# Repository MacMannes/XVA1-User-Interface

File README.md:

# XVA1 User Interface

A hardware user interface for the [XVA1 virtual analog synthesizer](https://www.futur3soundz.com/), inspired by the Hydrasynth's layout. The XVA1 (and its FM sibling the XFM2) is built on an Artix-7 FPGA but has no built-in UI — this project adds one.

## Overview

The UI board provides:

- **1 main rotary encoder** — patch selection and menu navigation
- **8 parameter rotary encoders** — control up to 8 synth parameters at once
- **4 OLED displays (128×64)** — show parameter names and values for each encoder pair
- **1 TFT display (240×240)** — main display showing patch name, section, and subsection
- **8 shortcut buttons with LEDs** — jump directly to parameter sections (Oscillators, Filters, Envelopes, LFOs, etc.). Hold SHIFT + buttons 1–4 to access sections 9–12
- **Up/Down buttons with LEDs** — scroll through parameter pages within a section

The design goal was minimal menu-diving: select a section with one button press, then tweak up to eight parameters directly with the encoders.

## Hardware

- **MCU:** Seeed XIAO ESP32-S3 (240 MHz, dual-core)
- **IO expansion:** 2× MCP23017 (the 8 parameter encoders connect via I2C)
- **Display mux:** TCA9548A I2C multiplexer for the 4 OLED displays
- **Synth connection:** UART at 500,000 baud (D6 TX, D7 RX)
- **PCB size:** 285 mm × 130 mm
- **Buttons:** PB86-B1 (with LED) / PB86-B0 (without LED), available from AliExpress

KiCad schematics are in the `Hardware/` directory.

## Build History

The project started in early 2021 on a breadboard with a Seeeduino XIAO (SAMD21), then moved to an ESP32 devboard when memory became a bottleneck, and eventually settled on the **Seeed XIAO ESP32-S3** as a drop-in replacement with the same footprint. The first PCB prototype was ordered from JLCPCB and had a few minor errors (MIDI DIN pin swap, resistor silkscreen mix-up) that were corrected in subsequent revisions.

## Software

### UI Board Firmware

Firmware source is in `Software/XVA1UserInterface/` and built with [PlatformIO](https://platformio.org/).

```bash
# Run from Software/XVA1UserInterface/
platformio run                  # compile
platformio run -t upload        # compile and flash
platformio run -t monitor       # open serial monitor (115200 baud)
./upload_and_monitor.sh         # flash then monitor
```

See `AGENTS.md` for a full architecture breakdown and development notes.

### Use in Neovim

In order to use this project in Neovim, you will have to create the file `compile_commands.json`
file by running the following command:

```bash
pio run -t compiledb
```

### Synth Management

To manage the XVA1 (or XFM/XFM2) synthesizer's own firmware and programs, use [**xload-macos**](https://github.com/MacMannes/xload-macos) — a macOS tool for managing flash memory on XFM/XFM2/XVA1 synthesizers.

## Project Structure

```
Hardware/       KiCad schematics and datasheets
Docs/           Photos of front and back of the board
Software/
  XVA1UserInterface/   PlatformIO project (all firmware lives here)
```

## Status

Working prototype. Most parameters are implemented and editable. Patch saving is not yet implemented. The PCB design has gone through two revisions; the current version uses the XIAO ESP32-S3.

## License

See `LICENSE.md`.

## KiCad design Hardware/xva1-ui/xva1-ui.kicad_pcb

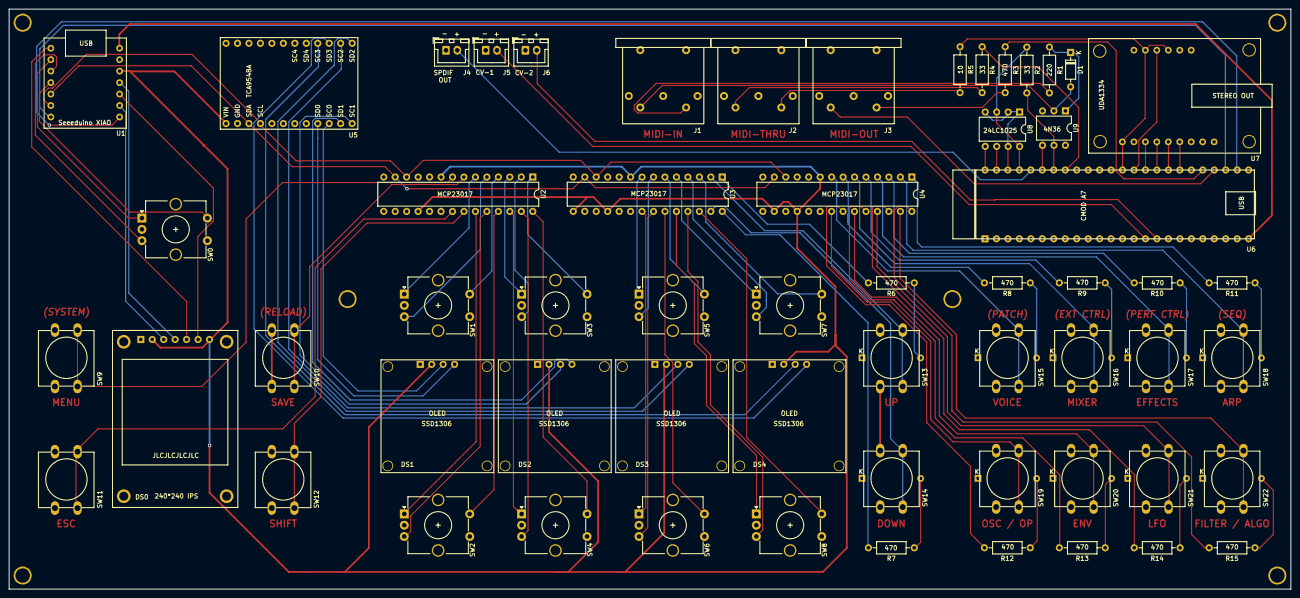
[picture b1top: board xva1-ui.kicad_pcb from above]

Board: 2 copper layers, 284.0 x 128.5 mm, 59 parts (0 on the bottom side), 104 nets.

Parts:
D1: 1N4148; D_DO-35_SOD27_P7.62mm_Horizontal
DS0: TFT_ST7789; TFT_IPS-240_240
DS1, DS2, DS3, DS4: SSD1306
J1, J2, J3: DIN-5_180degree; MIDI_CONNECTOR_PCB
J4, J5, J6: Conn_01x02; JST_XH_B2B-XH-A_1x02_P2.50mm_Vertical
R1: 220; R_Axial_DIN0207_L6.3mm_D2.5mm_P10.16mm_Horizontal
R2, R6, R7, R8, R9, R10, R11, R12, R13, R14, R15: 470; R_Axial_DIN0207_L6.3mm_D2.5mm_P10.16mm_Horizontal
R3, R4: 33; R_Axial_DIN0207_L6.3mm_D2.5mm_P10.16mm_Horizontal
R5: 10; R_Axial_DIN0207_L6.3mm_D2.5mm_P10.16mm_Horizontal
SW0, SW1, SW2, SW3, SW4, SW5, SW6, SW7, SW8: Rotary Encoder; RotaryEncoder_Alps_EC12E-Switch_Vertical_H20mm_CircularMoun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
SW9, SW10, SW11, SW12: SW_Push; SW_PUSH-12mm
SW13, SW14, SW15, SW16, SW17, SW18, SW19, SW20, SW21, SW22: SW_Push_LED; SW_PUSH_LED-12mm
U1: Seeeduino XIAO; Seeduino_XIAO_Through-Hole
U2, U3, U4: MCP23017; DIP-28_W7.62mm
U5: TCA9548A; TCA9548A_BREAKOUT
U6: CMOD-A7; CMOD-A7-DIP-48_W15.24mm
U7: UDA1334
U8: 24LC1025-I/P; DIP-8_W7.62mm
U9: 4N36; DIP-6_W7.62mm

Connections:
+3V3: DS0.2, DS0.7, DS1.2, DS2.2, DS3.2, DS4.2, U1.12, U2.9, U2.18, U3.9, U3.15, U3.18, U4.9, U4.16, U4.18, U5.1
+5V: U1.14, U6.24
/BTN-ESC: SW11.2, U2.21
/BTN-MENU: SW9.2, U2.8
/BTN-SAVE: SW10.2, U2.7
/BTN-SHIFT: SW12.2, U2.22
/ENC-A: SW0.A, U1.2
/ENC-B: SW0.B, U1.3
/ENC-S: SW0.S1, U1.4
/SCL: U1.6, U2.12, U3.12, U4.12, U5.4
/SDA: U1.5, U2.13, U3.13, U4.13, U5.3
BTN-DWN: SW14.2, U3.27
BTN-SC1: SW15.2, U4.8
BTN-SC2: SW16.2, U4.6
BTN-SC3: SW17.2, U4.4
BTN-SC4: SW18.2, U4.2
BTN-SC5: SW19.2, U4.21
BTN-SC6: SW20.2, U4.23
BTN-SC7: SW21.2, U4.25
BTN-SC8: SW22.2, U4.27
BTN-UP: SW13.2, U3.2
CV-INPUT-1: J5.2, U6.15
CV-INPUT-2: J6.2, U6.16
ENC1-A: SW1.A, U2.6
ENC1-B: SW1.B, U2.5
ENC1-S: SW1.S1, U2.4
ENC2-A: SW2.A, U2.23
ENC2-B: SW2.B, U2.24
ENC2-S: SW2.S1, U2.25
ENC3-A: SW3.A, U2.3
ENC3-B: SW3.B, U2.2
ENC3-S: SW3.S1, U2.1
ENC4-A: SW4.A, U2.26
ENC4-B: SW4.B, U2.27
ENC4-S: SW4.S1, U2.28
ENC5-A: SW5.A, U3.8
ENC5-B: SW5.B, U3.7
ENC5-S: SW5.S1, U3.6
ENC6-A: SW6.A, U3.21
ENC6-B: SW6.B, U3.22
ENC6-S: SW6.S1, U3.23
ENC7-A: SW7.A, U3.5
ENC7-B: SW7.B, U3.4
ENC7-S: SW7.S1, U3.3
ENC8-A: SW8.A, U3.24
ENC8-B: SW8.B, U3.25
ENC8-S: SW8.S1, U3.26
GND: DS0.1, DS1.1, DS2.1, DS3.1, DS4.1, J4.1, J5.1, J6.1, SW0.C, SW0.S2, SW1.C, SW1.S2, SW2.C, SW2.S2, SW3.C, SW3.S2, SW4.C, SW4.S2, SW5.C, SW5.S2, SW6.C, SW6.S2, SW7.C, SW7.S2, SW8.C, SW8.S2, SW9.1, SW10.1, SW11.1, SW12.1, SW13.1, SW13.3, SW14.1, SW14.3, SW15.1, SW15.3, SW16.1, SW16.3, SW17.1, SW17.3, SW18.1, SW18.3, SW19.1, SW19.3, SW20.1, SW20.3, SW21.1, SW21.3, SW22.1, SW22.3, U1.13, U2.10, U2.15, U2.16, U2.17, U3.10, U3.16, U3.17, U4.10, U4.15, U4.17, U5.2, U6.25
LED-DWN: R7.2, U3.28
LED-SC1: R8.2, U4.7
LED-SC2: R9.2, U4.5
LED-SC3: R10.2, U4.3
LED-SC4: R11.2, U4.1
LED-SC5: R12.2, U4.22
LED-SC6: R13.2, U4.24
LED-SC7: R14.2, U4.26
LED-SC8: R15.2, U4.28
LED-UP: R6.2, U3.1
unnamed: D1.1, R1.1, U9.1
unnamed: D1.2, J1.5, U9.2
unnamed: DS0.3, U1.9
unnamed: DS0.4, U1.11
unnamed: DS0.5, U1.1
unnamed: DS0.6, U1.10
unnamed: J1.4, R1.2
unnamed: J2.4, R5.1
unnamed: J2.5, R4.1
unnamed: J3.4, R3.1
unnamed: J3.5, U6.28
unnamed: R2.1, U6.45, U8.3, U8.8
unnamed: R2.2, U6.42, U9.5
unnamed: R3.2, U6.29
unnamed: R4.2, U6.41
unnamed: R5.2, U6.36, U7.1, U7.12, U7.14
unnamed: R6.1, SW13.4
unnamed: R7.1, SW14.4
unnamed: R8.1, SW15.4
unnamed: R9.1, SW16.4
unnamed: R10.1, SW17.4
unnamed: R11.1, SW18.4
unnamed: R12.1, SW19.4
unnamed: R13.1, SW20.4
unnamed: R14.1, SW21.4
unnamed: R15.1, SW22.4
unnamed: U6.31, U7.6
unnamed: U6.32, U7.5
unnamed: U6.33, U7.4
unnamed: U6.34, U7.3
unnamed: U6.35, U7.13
unnamed: U6.43, U9.4
unnamed: U6.46, U8.1, U8.2, U8.4, U8.7
unnamed: U6.47, U8.6
unnamed: U6.48, U8.5
OLED1-SCL: DS1.3, U5.10
OLED1-SDA: DS1.4, U5.9
OLED2-SCL: DS2.3, U5.12
OLED2-SDA: DS2.4, U5.11
OLED3-SCL: DS3.3, U5.14
OLED3-SDA: DS3.4, U5.13
OLED4-SCL: DS4.3, U5.16
OLED4-SDA: DS4.4, U5.15
SPDIF-OUT: J4.2, U6.44
XIAO-RX: U1.8, U6.26
XIAO-TX: U1.7, U6.27

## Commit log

2021-02-15 Added ino file
2021-02-15 Use rotary encoders with MCP23017
2021-02-16 Implemented displaying and changing of parameters
2021-02-17 Reformatting + added simple acceleraton for parameter encoders
2021-02-17 Added descriptions parameter values
2021-02-17 Fixed typo
2021-02-24 Implemented Performance Control Parameters
2021-02-24 Combined value of MSB + LSB should be int
2021-02-26 Implemented multiple oled diplays via TCA9548 i2c mux
2021-03-01 Small changes
2021-03-16 Added ShortcutButton1 (with LED) to prototype
2021-03-16 Refactoring: Moved code to Software + Added Hardware
2021-03-16 Added resistors to LED buttons
2021-03-16 Updated PCB layout + Added Gerber files
2021-03-17 Changed mounting holes + board outline
2021-03-23 Moved to PlatformIO
2021-03-23 Lock mounting holes
2021-03-24 Added LEDButton class
2021-04-01 Implemented shortcut-button handling
2021-04-01 Refactoring
2021-04-02 Added Button class + created instances for all buttons
2021-04-02 Added mainRotaryEncoder
2021-04-03 Oops: switched PRESSED and RELEASED
2021-04-03 Pin A and Pin B of the rotary encoder were switched
2021-04-03 Added upload_and_monitor script
2021-04-03 Added Up, Down and Main Rotary buttons
2021-04-04 Added SynthParameterBuilder
2021-04-04 Rename create() method to build()
2021-04-04 Remove unnecessary initializers
2021-04-04 Implemented descriptions of SynthParameter with std::vector
2021-04-05 Prepare for creating all parameters in XVA1Synthparameters.h
2021-04-05 Added bitNumber to SynthParameter
2021-04-05 Fixed bug
2021-04-05 Small change
2021-04-06 Added Section class + some more parameters
2021-04-06 Create SynthParameters directly in a section, to save some memory
2021-04-07 Added Synthesizer class
2021-04-07 Changed text size and colors of main screen
2021-04-08 remove getPatchData()
2021-04-08 Added Multiplexer class
2021-04-08 Moved displays to Hardware.h
2021-04-08 Use pin names in stead of numbers + added all rotary encoders
2021-04-08 Added ParameterController
2021-04-09 Added logic to ParameterController
2021-04-10 Fix for parameter value descriptions that were too big
2021-04-10 Added CENTER_128 to ParameterType
    128 is the center value and can be used for easier reading of transpose value etc.
2021-04-10 Made a start with sections
2021-04-11 Page number = now zero based + prepare for real subsections
2021-04-11 Added subections
2021-04-12 Implemented displaying and selection of subsections
2021-04-13 Improved displaying of subsections
2021-04-13 Made several improvements in displaying screen data
2021-04-14 Added some more parameters + implemented BITWISE parameters
2021-04-14 Added more parameters
2021-04-16 Refactoring to improve memory usage
2021-04-17 Added more parameters
    Note: Parameters for External Controls are commented-out, because of memory problems
2021-04-20 Refactoring to save some more memory
2021-04-20 Renamed some parameters
2021-04-23 Switched to esp32
2021-04-27 Always display "> Main" when there are no subsections
2021-04-28 Added even more parameters
2021-04-30 All sections are now kept in memory + added rudimentary way to change patch name
2021-04-30 Added graphs for envelopes
2021-04-30 Switched Rate and Level pages of Envelope section + small changes
2021-05-01 Added VELO SENS paramerer
2021-05-01 Use task to display envelopes
2021-05-01 Change type of Pitch envelope levels
2021-05-04 Use interrupts for main rotary encoder + button
2023-08-04 Revert "Use interrupts for main rotary encoder + button"
    This reverts commit 3dcfe536afd948128d9f93f24c43c69807b91256.
2023-08-06 Changed board to Seeed Studio XIAO ESP32S3
2026-05-27 feat: added AGENTS.md
2026-05-27 feat: added readme
2026-05-30 fix: move SynthSerial from UART0 to UART1 to eliminate conflict with Serial
    SynthSerial was instantiated on UART0 (HardwareSerial(0)), the same
    peripheral used by Serial for debug output. This caused both to stomp
    over each other during synth communication.
    Fixed by:
    - Changing SynthSerial to UART1 (HardwareSerial(1))
    - Explicitly passing GPIO43 (D6/TX) and GPIO44 (D7/RX) in begin(),
2026-05-30 refactor: replace Serial debug calls with compile-time LOG macros; enable USB CDC
    Introduce src/Debug.h with LOG/LOGLN/LOG_BEGIN macros that forward to
    Serial when -D DEBUG is set, and expand to nothing in production builds.
    All 53 raw Serial.print/println calls across main.cpp, Synthesizer.cpp
    and ParameterController.cpp are replaced with these macros.
    platformio.ini changes:
    - Add -D ARDUINO_USB_CDC_ON_BOOT=1: Serial becomes USB CDC on the
2026-05-31 fix: flush UART TX buffer after setParameter to prevent command misalignment
    Several parameter numbers coincide with destructive synth command bytes
    (116 = 't' tuning write, 86 = 'V' wavetable erase, 125 = '}' EEPROM
    write). If rapid back-to-back calls overflow the synth's UART FIFO and
    the leading 's' byte is dropped, the parameter number is interpreted as
    a command, corrupting flash.
    SynthSerial.flush() blocks until all bytes are physically sent (~60 µs
2026-05-31 fix: pin espressif32 platform to 6.3.2 for TFT_eSPI compatibility
    Arduino ESP32 3.x (platform 6.10.0+) has incompatibility with TFT_eSPI 2.5.43
    on ESP32-S3, causing SPI initialization failure at boot. Pinning to 6.3.2
    (Arduino ESP32 2.x) resolves the issue.
    Also includes prior fixes:
    - Increased displayEnvelopesTask stack size from 1000 to 4096 words
    - Added guard to prevent multiple concurrent envelope rendering tasks
2026-05-31 docs: update AGENTS.md with platform pinning and recent fixes
    - Document platform version pinning to espressif32@6.3.2
    - Add manual upload procedure for bootloader mode
    - Document FreeRTOS envelope rendering task fixes
    - Add Known Issues & Fixes section with TFT compatibility details
    - Clarify USB CDC and Serial configuration
2026-05-31 docs: add Dependency Management section for platform/tool updates
    - Clarify that platformio CLI updates are safe
    - Document why espressif32 platform is pinned to 6.3.2
    - Provide procedure for safely testing platform upgrades
    - Explain library version management in platformio.ini
2026-05-31 docs: add detailed espressif32 platform upgrade guide
    - Explain why currently pinned to 6.3.2
    - Provide upgrade path when TFT_eSPI adds ESP32 3.x support
    - Document testing and rollback procedures
    - List alternative libraries (LovyanGFX) if needed
    - Add monitoring resources for library updates
2026-05-31 docs: add information about xload-macos
2026-06-01 fix: clamp PERFORMANCE_CTRL values to 0-511 range
    MIDI performance controls should allow values 0-511 to cover all
    parameters of the XVA1 synth. Previously limited to 0-255 due to
    the generic uint8_t min/max clamping logic.
    Fixes #1
2026-06-01 chore: add .clang-format and configured project to be editted by NeoVim
2026-06-05 style: reformat code
2026-06-05 fix: add includes to fix warnings
